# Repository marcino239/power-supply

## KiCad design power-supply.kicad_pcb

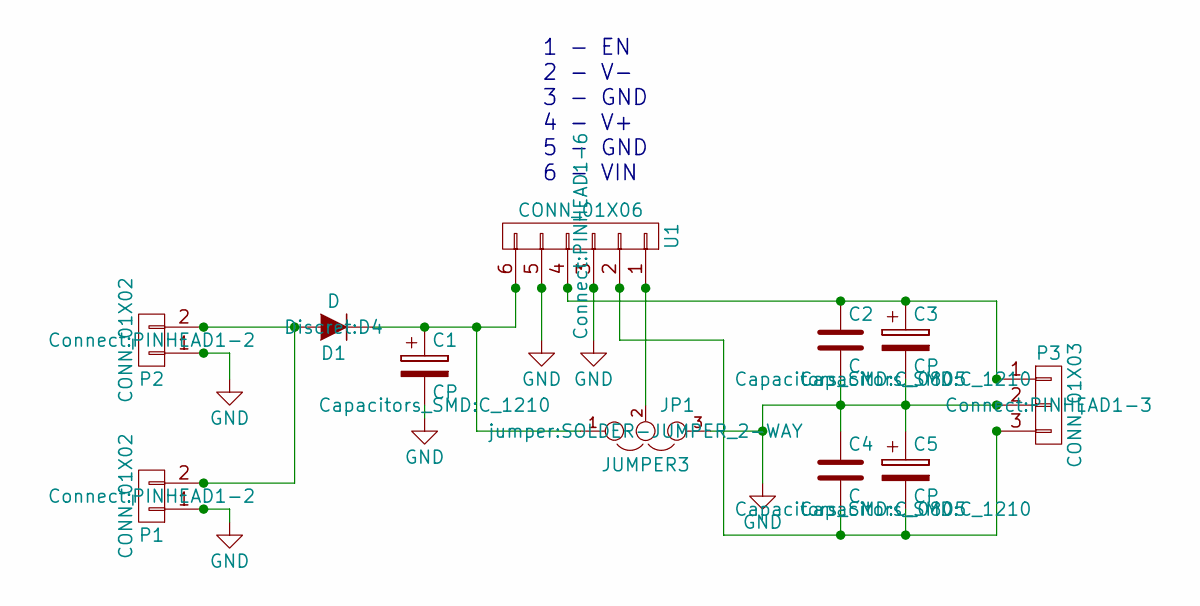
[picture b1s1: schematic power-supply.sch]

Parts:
C1, C3, C5: CP; C_1210
C2, C4: C; C_0805
D1: D; D4
JP1: JUMPER3; SOLDER-JUMPER_2-WAY
P1, P2: CONN_01X02; PINHEAD1-2
P3: CONN_01X03; PINHEAD1-3
U1: CONN_01X06; PINHEAD1-6

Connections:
GND: C1.2, C2.2, C3.2, C4.1, C5.1, JP1.3, P1.1, P2.1, P3.2, U1.3, U1.5
unnamed: C1.1, D1.1 (K), JP1.1, U1.6
unnamed: C2.1, C3.1, P3.1, U1.4
unnamed: C4.2, C5.2, P3.3, U1.2
unnamed: D1.2 (A), P1.2, P2.2
unnamed: JP1.2, U1.1

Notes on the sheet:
1 - EN 2 - V- 3 - GND 4 - V+ 5 - GND 6 - VIN

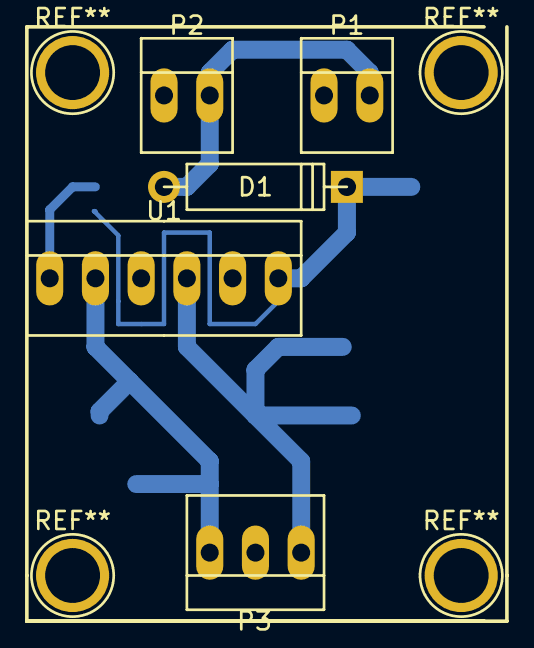
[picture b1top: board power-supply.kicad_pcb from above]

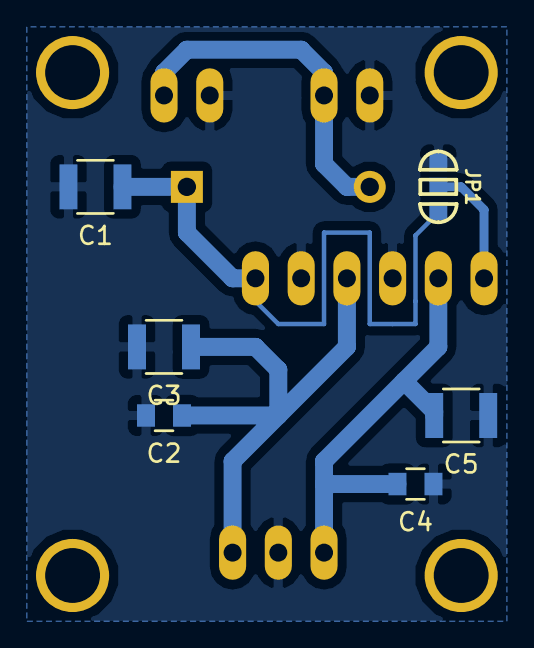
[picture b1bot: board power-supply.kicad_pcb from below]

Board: 2 copper layers, 11 parts (6 on the bottom side), 6 nets.

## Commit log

2016-08-05 initial version
2016-08-05 added board
2016-08-08 final version
